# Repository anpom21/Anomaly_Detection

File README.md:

# Leg press mechanics project

This code is for the mechanics project were our group has made a leg press.
The main file in this project is located under the Interface folder, and its the GUI.py file.
This file runs the GUI for the project and calls all the relevant modules from other folders.
The game can be ran as an individual file using the file in the Interface/Game folder called flappy_bird.py. 
The file should be run from the interface folder. Ensure that all the required dependencies listed below are installed.

# Dependencies

The project is tested with python 3.10 and 3.12. The packages required can be found in "Interface/requirements.txt" or below here:
- pyserial
- pygame
- websocket-client
- websockets
- PySide6
- matplotlib
- numpy
- PyYAML
- pyqtgraph
- PyQt6

A python environment can be made with "python -m venv .venv". After activating the environment, the packages can be installed with pip install -r "Interface/requirements.txt".

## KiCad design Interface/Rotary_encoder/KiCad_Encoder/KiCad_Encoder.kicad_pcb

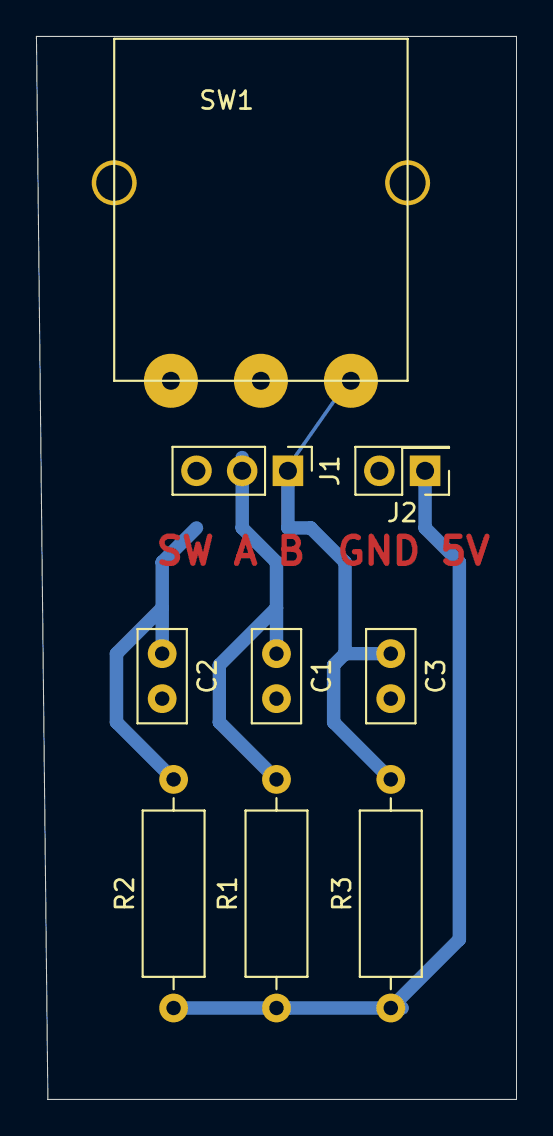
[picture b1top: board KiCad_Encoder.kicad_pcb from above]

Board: 2 copper layers, 26.7 x 59.1 mm, 9 parts (0 on the bottom side), 5 nets.

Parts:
C1, C2, C3: 100nF; C_Disc_D5.0mm_W2.5mm_P2.50mm
J1: MIC; PinHeader_1x03_P2.54mm_Vertical
J2: Vcc + GND; PinHeader_2x01_P2.54mm_Vertical
R1, R2, R3: 10kOhm; R_Axial_DIN0309_L9.0mm_D3.2mm_P12.70mm_Horizontal
SW1: Rotary_Encoder_Switch; Rotary_Encoder_pantilt

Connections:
+5V: J2.1, R1.1, R2.1, R3.1
GND: C1.2, C2.2, C3.2, J2.2
unnamed: C3.1, J1.1, R3.2, SW1.C
unnamed: C1.1, J1.2, R1.2, SW1.A
unnamed: C2.1, J1.3, R2.2, SW1.B

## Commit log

2025-03-05 First commit
    Trained an auto encoder (later found ipynb with all code) and added ipynb with more advanced network that uses resnet50 as backbone and autoencoder for anomaly heatmap.
2025-03-05 patchcore ipynb
2025-03-06 Dataset1
    Added Dataset1
2025-03-06 requirements
2025-03-06 Playing with channels
    I tested the autoencoders ability to deal with more than 3 channels and changed the autoencoder to take images with 4 channels
2025-03-06 Preprocessing v1
2025-03-06 Main gitignore
2025-03-06 preprocessing v2
2025-03-07 Trying to load data from np.array
2025-03-11 load_np
    Fixed load data to load 4-channel images from np.arrays
2025-03-11 Added empty labels to data
2025-03-11 Model can train
2025-03-13 Added processing of test data
2025-03-13 Dataset001 groundTruth
2025-03-13 Saved RCerror images
2025-03-13 Leg_press branched added
2025-03-13 Processed data
    Added test to save the reconstruction error
2025-03-14 git connection test
2025-03-14 UR RTDE visualisation
2025-03-14 RTDE visualization
2025-03-14 Working on RTDE
2025-03-15 UR RTDE working well, code clean up needed
2025-03-18 A_Beam
2025-03-20 Lightbracket
2025-03-20 Added object center for real robot
2025-03-24 Postprocessing attempt
2025-03-25 Parallel beams and hinge
2025-03-27 Preprocessing
2025-03-27 Oops
2025-03-27 Added ResNet50-101-152
2025-03-28 Code cleanup
2025-03-28 Preparing for IRL data collection
2025-03-28 More data collection prep
2025-03-29 Training works?
2025-03-29 Attempt at ResNet50 Backbone
2025-03-30 simplenet_3_resnet50
2025-03-30 carema code
2025-04-02 Added possible ResNet50 feature extractor
2025-04-02 Update .gitignore
    Added .venv to .gitignore
2025-04-03 B_beam
2025-04-03 Dataset002
2025-04-03 Tried to train a feature extractor + autoencoder (Successfull training - bad result)
2025-04-03 Processed new dataset
2025-04-03 Trained new autoencoder
2025-04-06 Tried Different autoencoders
2025-04-08 Data collection progress
2025-04-08 Piston_Bottom_Hinge
2025-04-08 B and C first iteration done
2025-04-09 Piston hinge to A beam
2025-04-10 TestForHome
2025-04-10 DeeperWiderFixedWithThreshold
2025-04-20 Dataset 3
2025-04-21 Late night push
2025-04-22 unimportant push
2025-04-22 22/04 push
2025-04-22 autoencoder
2025-04-24 Thursday stuff :)
2025-04-24 clean up
2025-04-24 Cleanup for merge
2025-04-24 Further Cleanup
2025-04-24 Lighttest
    Started writing the light source check. Far from done
2025-04-29 first time fully assembled
2025-04-29 Extended base plate
2025-04-29 Leg Press - Interface
2025-04-30 Prep for sim
2025-04-30 Simulated
2025-04-30 sim...
2025-05-01 WorkingOnLighttest
    We need to modify Dataloader to both load train and test data and give labels to test data. Then we need to make sure testfunction works. Then we should try to run light test, to train networks with 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
2025-05-01 Dataloader works, now we have to test validation
2025-05-01 Refactoring of dataloader
2025-05-02 Added simulation trial run
2025-05-02 IK solver works better
2025-05-02 Fixed Lighttest
2025-05-05 MSE Thresholding
2025-05-06 NoBlocks
2025-05-06 URRTDE progress
2025-05-06 Legpress game
2025-05-06 InitGUI
    We need the pygame to embed, and make some beauty changes and add correct calculation functions
2025-05-06 GUI.py+game
    Updated GUI.py so that game is integrated, but it is currently not taking inputs. Need to implement heartbeat readings as well
2025-05-06 Game beautified
2025-05-06 Game smoothing
2025-05-06 Integrated into gui - somewhat..
2025-05-06 RotationTest
    Test to see if training the model on data that is rotated affects the outcome. spoiler it does!
2025-05-06 ReadyForBigLightTest
2025-05-07 GUI working with game
2025-05-07 Pressure_measurements
2025-05-07 Dataset4
2025-05-07 Update to very big models
2025-05-07 Changed .gitignore to include pressure measurements
2025-05-07 IRL data generation now ready
2025-05-07 First IRL data
2025-05-07 Updated LightTest
    Something whent wrong in the dataloader and it all whent to shit. Well... That was one day...
2025-05-07 dataset004 test_easy
2025-05-08 Blemish test set
2025-05-08 leg press v4
2025-05-08 ThresholdTestSucces
2025-05-09 First 94 IRL samples
2025-05-10 4 channels real dataset acquired
2025-05-11 updated .gitignore
2025-05-11 IRL dataset
2025-05-11 Moved dataset
2025-05-11 LightTestResults
2025-05-12 Specific light test on ResNetAutoencoder
2025-05-12 Renaming of Real dataset
2025-05-12 Resize of Real data
2025-05-12 Figures for light test
    Thoughts: how deep does the network have to be in order to astract from rotation and placement
    Flad lys vs 1 vinklet lyskilde vs flere vinklet lyskilder?
    Statisiske metoder vs neural network metoder. Kan vi bevise
    Lav dataset med 8 lyskilder og flad lys. Gerne med færer ridser. Gode eksempler i test datasættet.
    Simuleret vs rigtig data.
2025-05-13 after cut
2025-05-14 Averaging method
2025-05-14 3 channel dataset + 4 channel small defects
2025-05-14 Patch core
2025-05-14 Patchcore
2025-05-14 TestsOfModelsPerformanceOnIRLData
    Here is a mixture of figures made from training the models on IRL data and how they localize anomalies.
2025-05-20 Game fixed?
2025-05-20 Game is now working, and GUI reads BPM too
2025-05-20 Hot fixes
    Added extra tab for velocity and power plot. made gui full screen and native resolution.
2025-05-20 *Beautiy*
    Fixed some things in the GUI. Added Louises code for the potentiometer
2025-05-20 Hot fixes *Fire emoji*
2025-05-22 foot plate
2025-05-22 Changed beam ends
2025-05-24 Game Changes
2025-05-27 quick push
2025-05-27 Bushings, potmeter, shaft interface, and minor changes
2025-05-27 Aluminium leg press simulation done
2025-05-27 Changed requirements
2025-05-27 Updated GUI
2025-05-27 Abs(power)
2025-05-27 GAME: Restart fixed
2025-05-27 Recorded Data
2025-05-27 Game works on leg press, not on GUI yet tho
2025-05-27 Human AD
2025-05-27 Human AD real
2025-05-27 LightTestV2
2025-05-28 report prep
2025-05-28 LightTestV2Update
2025-05-29 Game improvements
2025-06-01 Game works with GUI, but still lags
2025-06-02 actual m/s
2025-06-02 some changes
2025-06-03 final push
2025-07-02 late merge
2025-07-09 Fixed game
